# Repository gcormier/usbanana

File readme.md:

# usbanana

USB is great - endless 5V power supplies to be used on many projects. As a result, I design a lot of things with it, and you might as well.

While there are many USB power meters to show current/voltage information, I wanted a way to use the current-limiting features of my power supply when I first plug in a design so nothing goes boom. Assuming that's the case, I can then also see what sort of current draw the device has.

The banana spacing is adjustable as well since it would appear the standard for banana plugs is not a standard in some cases. There is a spot for either through-hole or SMT resistors across data lines if your device is smart enough to check for that.

# Storage
If you would to purchase a pre-made version, you can get it on my store <a href="https://www.tindie.com/products/gcormier/usbanana/">usbanana</a>

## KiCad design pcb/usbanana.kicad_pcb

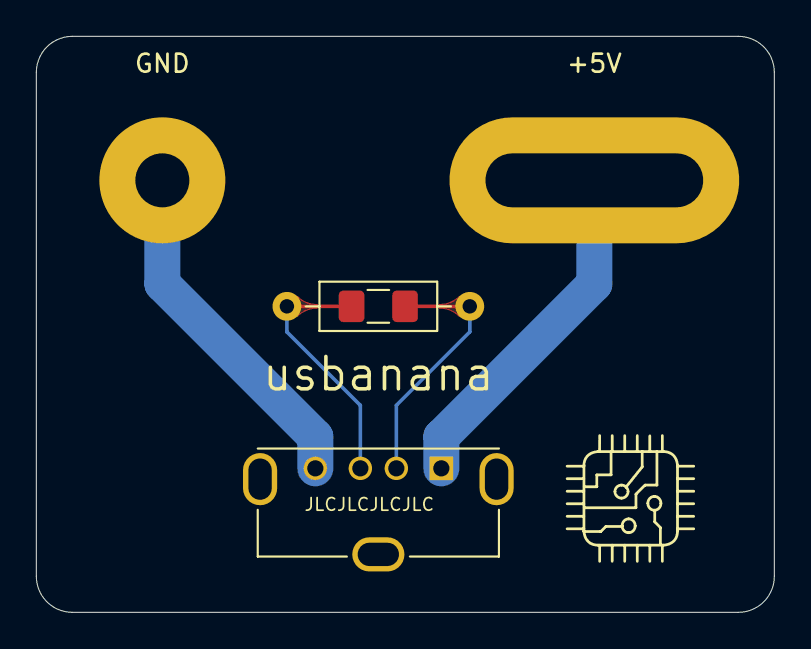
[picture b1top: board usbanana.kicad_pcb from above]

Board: 2 copper layers, 41.0 x 32.0 mm, 5 parts (0 on the bottom side), 4 nets.

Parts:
+5V: 5V; Banana_Jack_Slot
J1: USB_A; USB_A_Molex_105057_Vertical
J3: GND; Banana_Jack_1Pin
R1: OPT; R_1206_3216Metric_Pad1.42x1.75mm_HandSolder
R2: OPT; R_Axial_DIN0207_L6.3mm_D2.5mm_P10.16mm_Horizontal

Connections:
unnamed: +5V.1, J1.1
unnamed: J1.2, R1.2, R2.2
unnamed: J1.3, R1.1, R2.1
unnamed: J1.4, J3.1

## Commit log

2020-09-18 initial
2020-09-18 docs
2020-09-18 formatting
